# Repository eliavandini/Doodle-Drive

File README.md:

# Doodle-Drive
[Dokumentation](https://drive.google.com/file/d/1KEJBJEgJQQi80HQPX5YeS3n4wLadLSkT/view?usp=drive_link)

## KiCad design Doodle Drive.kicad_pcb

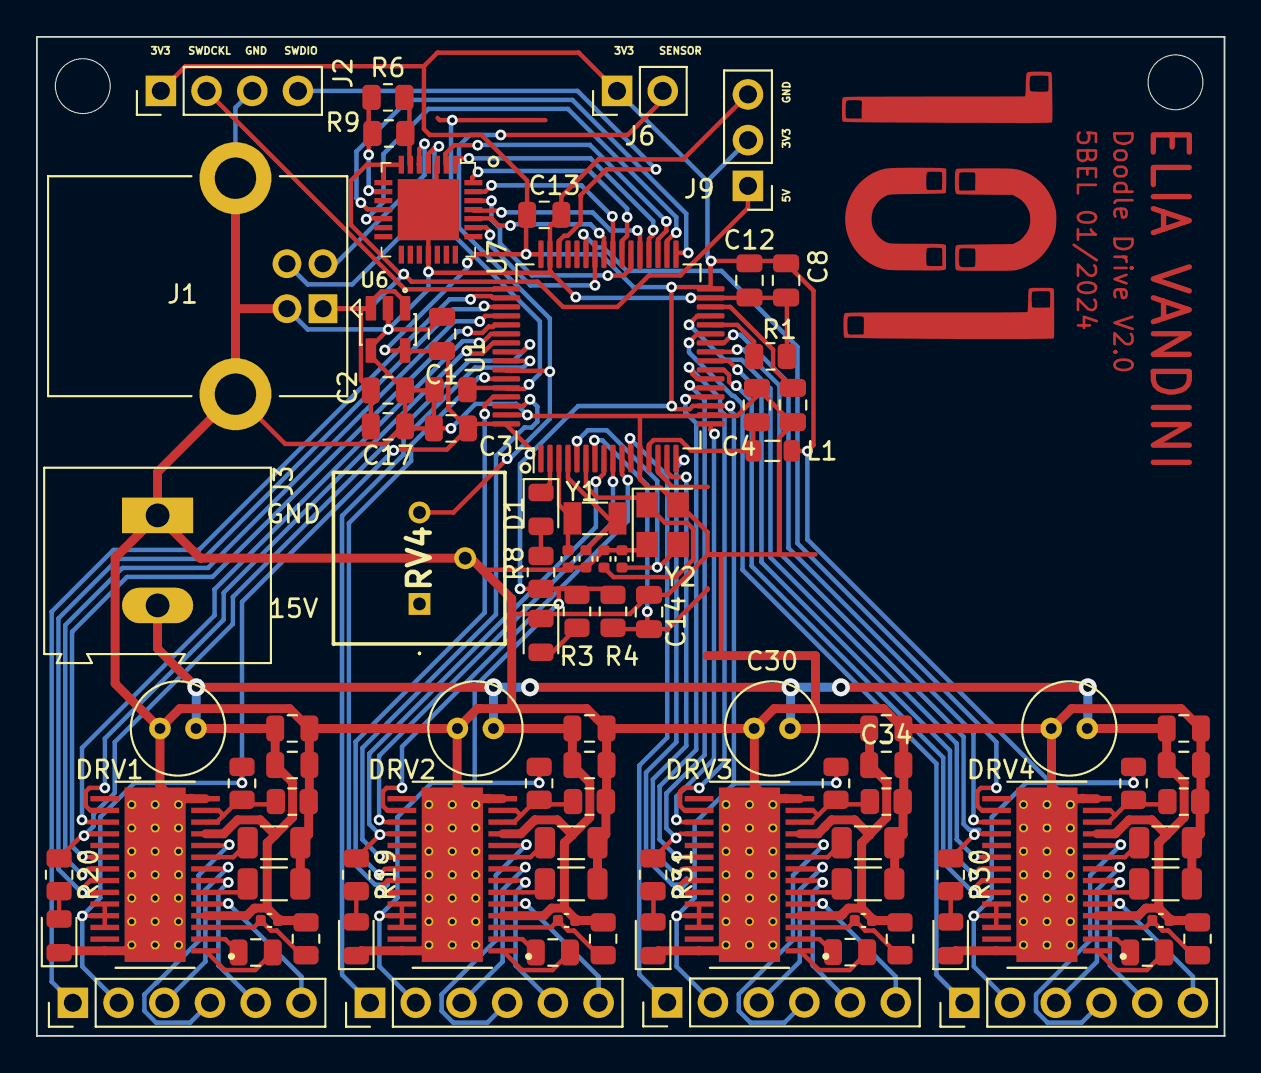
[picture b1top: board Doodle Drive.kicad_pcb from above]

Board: 2 copper layers, 66.0 x 55.5 mm, 91 parts (0 on the bottom side), 105 nets.

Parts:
C1, C17: 1uF; C_0805_2012Metric
C2, C3, C4, C8, C12, C13, C14, C20, C21, C23, C24, C31, C32, C33, C34: 100nF; C_0805_2012Metric
C5, C15, C25, C26: 10nF; C_0805_2012Metric
C6, C9: 18pF; C_0402_1005Metric
C7, C10: 15pF; C_0402_1005Metric
C11, C16, C27, C28: 100nF; C_0402_1005Metric
C18, C22, C29, C30: 10uF; C_Radial_D5.0mm_H5.0mm_P2.00mm
C19: 2.2uF; C_0805_2012Metric
D1: LED_GREEN; LED_0805_2012Metric
D2, D3, D4, D5, D6: LED_RED; LED_0805_2012Metric
DRV1, DRV2, DRV3, DRV4: DRV8825PWP; IC_TPS61196PWPRQ1
J1: USB_B; USB_B_Lumberg_2411_02_Horizontal
J2: PINHD_1x4_Male; PinHeader_1x04_P2.54mm_Vertical
J3: Screw_Terminal_01x02; TerminalBlock_Altech_AK300-2_P5.00mm
J4, J5, J7, J8: PINHD_1x6_Male; PinHeader_1x06_P2.54mm_Vertical
J6: PINHD_1x2_Male; PinHeader_1x02_P2.54mm_Vertical
J9: PINHD_1x3_Male; PinHeader_1x03_P2.54mm_Vertical
L1: 10uH; L_0805_2012Metric
R1, R2: 10k; R_0805_2012Metric
R3, R8, R19, R20, R30, R31: 5.1k; R_0805_2012Metric
R4: 0ohm; R_0805_2012Metric
R5, R7, R10, R22: 15k; R_0805_2012Metric
R6: 8.2k; R_0805_2012Metric
R9: 11k; R_0805_2012Metric
R11, R12, R21, R23: 9.1k; R_0805_2012Metric
R13, R14, R15, R16, R24, R25, R26, R27: 100m; R_1206_3216Metric
R17, R18, R28, R29: 1M; R_0805_2012Metric
RV4: R_Potentiometer; 3386P1473LF
U1: STM32F411RETx; LQFP-64_10x10mm_P0.5mm
U6: AP7343-33W5-7; SOT95P285X145-5N
U7: CP2102-GMR; VFQFN-28-1EP_5x5mm
Y1: 32.768KHz ±20ppm 12.5pF; Crystal_SMD_3215-2Pin_3.2x1.5mm
Y2: 25MHZ 12PF; Crystal_SMD_3225-4Pin_3.2x2.5mm

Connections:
+3V3: C1.2, C3.2, C8.2, C12.2, C13.2, DRV1.24 (MODE0), DRV1.25 (MODE1), DRV1.26 (MODE2), DRV2.24 (MODE0), DRV2.25 (MODE1), DRV2.26 (MODE2), DRV3.24 (MODE0), DRV3.25 (MODE1), DRV3.26 (MODE2), DRV4.24 (MODE0), DRV4.25 (MODE1), DRV4.26 (MODE2), J2.1, J4.2, J5.2, J6.1, J7.2, J8.2, J9.2, L1.1, R3.2, R4.2, R5.2, R7.2, R8.2, R10.2, R22.2, U1.19 (VDD), U1.32 (VDD), U1.48 (VDD), U1.64 (VDD), U6.5 (VOUT)
+5V: C2.2, C17.1, J1.1 (VBUS), J9.1, U6.1 (VIN), U6.3 (EN), U7.7 (REGIN), U7.8 (VBUS)
+15V: C11.1, C16.1, C18.2, C20.1, C21.1, C22.2, C23.1, C24.1, C27.1, C28.1, C29.2, C30.2, C31.1, C32.1, C33.1, C34.1, DRV1.4 (VMA), DRV1.11 (VMB), DRV2.4 (VMA), DRV2.11 (VMB), DRV3.4 (VMA), DRV3.11 (VMB), DRV4.4 (VMA), DRV4.11 (VMB), J3.2, R17.2, R18.2, R28.2, R29.2
BOOT0: R2.1, U1.60 (BOOT0)
DIR1: DRV1.20 (DIR), U1.53 (PC12)
DIR2: DRV2.20 (DIR), U1.62 (PB9)
DIR3: DRV3.20 (DIR), U1.20 (PA4)
DIR4: DRV4.20 (DIR), U1.29 (PB10)
GND: C1.1, C2.1, C3.1, C4.1, C6.1, C7.1, C8.1, C9.1, C10.2, C12.1, C13.1, C14.1, C17.2, C18.1, C19.2, C20.2, C21.2, C22.1, C23.2, C24.2, C29.1, C30.1, C31.2, C32.2, C33.2, C34.2, D2.1 (K), D3.1 (K), D4.1 (K), D5.1 (K), D6.1 (K), DRV1.14 (GND), DRV1.28 (GND), DRV1.29 (EXP), DRV1.30 (EXP), DRV1.31 (EXP), DRV1.32 (EXP), DRV1.33 (EXP), DRV1.34 (EXP), DRV1.35 (EXP), DRV1.36 (EXP), DRV1.37 (EXP), DRV1.38 (EXP), DRV1.39 (EXP), DRV1.40 (EXP), DRV1.41 (EXP), DRV1.42 (EXP), DRV1.43 (EXP), DRV1.44 (EXP), DRV1.45 (EXP), DRV1.46 (EXP), DRV1.47 (EXP), DRV1.48 (EXP), DRV1.49 (EXP), DRV1.50 (EXP), DRV2.14 (GND), DRV2.28 (GND), DRV2.29 (EXP), DRV2.30 (EXP), DRV2.31 (EXP), DRV2.32 (EXP), DRV2.33 (EXP), DRV2.34 (EXP), DRV2.35 (EXP), DRV2.36 (EXP), DRV2.37 (EXP), DRV2.38 (EXP), DRV2.39 (EXP), DRV2.40 (EXP), DRV2.41 (EXP), DRV2.42 (EXP), DRV2.43 (EXP), DRV2.44 (EXP), DRV2.45 (EXP), DRV2.46 (EXP), DRV2.47 (EXP), DRV2.48 (EXP), DRV2.49 (EXP), DRV2.50 (EXP), DRV3.14 (GND), DRV3.28 (GND), DRV3.29 (EXP), DRV3.30 (EXP), DRV3.31 (EXP), DRV3.32 (EXP), DRV3.33 (EXP), DRV3.34 (EXP), DRV3.35 (EXP), DRV3.36 (EXP), DRV3.37 (EXP), DRV3.38 (EXP), DRV3.39 (EXP), DRV3.40 (EXP), DRV3.41 (EXP), DRV3.42 (EXP), DRV3.43 (EXP), DRV3.44 (EXP), DRV3.45 (EXP), DRV3.46 (EXP), DRV3.47 (EXP), DRV3.48 (EXP), DRV3.49 (EXP), DRV3.50 (EXP), DRV4.14 (GND), DRV4.28 (GND), DRV4.29 (EXP), DRV4.30 (EXP), DRV4.31 (EXP), DRV4.32 (EXP), DRV4.33 (EXP), DRV4.34 (EXP), DRV4.35 (EXP), DRV4.36 (EXP), DRV4.37 (EXP), DRV4.38 (EXP), DRV4.39 (EXP), DRV4.40 (EXP), DRV4.41 (EXP), DRV4.42 (EXP), DRV4.43 (EXP), DRV4.44 (EXP), DRV4.45 (EXP), DRV4.46 (EXP), DRV4.47 (EXP), DRV4.48 (EXP), DRV4.49 (EXP), DRV4.50 (EXP), J1.4 (GND), J1.5 (Shield), J2.3, J3.1, J9.3, R1.1, R2.2, R11.1, R12.1, R13.2, R14.2, R15.2, R16.2, R21.1, R23.1, R24.2, R25.2, R26.2, R27.2, RV4.2, U1.12 (VSSA), U1.18 (VSS), U1.31 (VSS), U1.47 (VSS), U1.63 (VSS), U6.2 (GND), U6.4 (NC), U7.3 (GND), U7.18 (VPP), U7.29 (GND_PAD), Y2.2, Y2.4
unnamed: D1.2 (A), R8.1
unnamed: D2.2 (A), R3.1
unnamed: D3.2 (A), R19.2
unnamed: D4.2 (A), R20.2
unnamed: D5.2 (A), R30.2
unnamed: D6.2 (A), R31.2
unnamed: DRV1.5 (AOUT1), J5.6
unnamed: DRV1.7 (AOUT2), J5.5
unnamed: DRV1.12 (AVREF), DRV1.13 (BVREF), R7.1, R21.2
unnamed: DRV1.10 (BOUT1), J5.4
unnamed: DRV1.8 (BOUT2), J5.3
unnamed: C15.2, DRV1.1 (CP1)
unnamed: C15.1, DRV1.2 (CP2)
unnamed: DRV1.6 (ISENA), R15.1
unnamed: DRV1.9 (ISENB), R16.1
unnamed: C16.2, DRV1.3 (VCP), R17.1
unnamed: DRV2.5 (AOUT1), J7.6
unnamed: DRV2.7 (AOUT2), J7.5
unnamed: DRV2.12 (AVREF), DRV2.13 (BVREF), R5.1, R12.2
unnamed: DRV2.10 (BOUT1), J7.4
unnamed: DRV2.8 (BOUT2), J7.3
unnamed: C5.2, DRV2.1 (CP1)
unnamed: C5.1, DRV2.2 (CP2)
unnamed: DRV2.6 (ISENA), R13.1
unnamed: DRV2.9 (ISENB), R14.1
unnamed: C11.2, DRV2.3 (VCP), R18.1
unnamed: DRV3.5 (AOUT1), J8.6
unnamed: DRV3.7 (AOUT2), J8.5
unnamed: DRV3.12 (AVREF), DRV3.13 (BVREF), R22.1, R23.2
unnamed: DRV3.10 (BOUT1), J8.4
unnamed: DRV3.8 (BOUT2), J8.3
unnamed: C26.2, DRV3.1 (CP1)
unnamed: C26.1, DRV3.2 (CP2)
unnamed: DRV3.6 (ISENA), R26.1
unnamed: DRV3.9 (ISENB), R27.1
unnamed: C28.2, DRV3.3 (VCP), R29.1
unnamed: DRV4.5 (AOUT1), J4.6
unnamed: DRV4.7 (AOUT2), J4.5
unnamed: DRV4.12 (AVREF), DRV4.13 (BVREF), R10.1, R11.2
unnamed: DRV4.10 (BOUT1), J4.4
unnamed: DRV4.8 (BOUT2), J4.3
unnamed: C25.2, DRV4.1 (CP1)
unnamed: C25.1, DRV4.2 (CP2)
unnamed: DRV4.6 (ISENA), R24.1
unnamed: DRV4.9 (ISENB), R25.1
unnamed: C27.2, DRV4.3 (VCP), R28.1
unnamed: J1.3 (D+), U7.4 (D+)
unnamed: J1.2 (D-), U7.5 (D-)
unnamed: C19.1, U1.30 (VCAP1)
unnamed: R6.1, R9.1, U7.9 (RST)
unnamed: R6.2, R9.2, U7.6 (VDD)
PA1: DRV3.21 (NENBL), U1.15 (PA1)
PA2: DRV3.22 (STEP), U1.16 (PA2)
PA3: DRV3.17 (NSLEEP), U1.17 (PA3)
PA5: DRV3.18 (NFAULT), R31.1, U1.21 (PA5)
PA6: DRV3.16 (~NRESET), U1.22 (PA6)
PA7: DRV4.22 (STEP), U1.23 (PA7)
PA8: U1.41 (PA8), U7.24 (~RTS)
PA9: U1.42 (PA9), U7.23 (~CTS)
PA10: DRV4.16 (~NRESET), U1.43 (PA10)
PA13: J2.4, U1.46 (PA13)
PA14: J2.2, U1.49 (PA14)
PA15: J5.1, U1.50 (PA15)
PB0: DRV4.17 (NSLEEP), U1.26 (PB0)
PB1: J4.1, U1.27 (PB1)
PB2: R1.2, U1.28 (PB2)
PB3: DRV1.16 (~NRESET), U1.55 (PB3)
PB4: DRV1.18 (NFAULT), R20.1, U1.56 (PB4)
PB5: J7.1, U1.57 (PB5)
PB6: J6.2, RV4.3, U1.58 (PB6)
PB7: DRV2.22 (STEP), U1.59 (PB7)
PB8: DRV2.21 (NENBL), U1.61 (PB8)
PB12: U1.33 (PB12), U7.11 (~SUSPEND)
PB13: U1.34 (PB13), U7.12 (SUSPEND)
PB14: U1.35 (PB14), U7.2 (~RI)
PB15: U1.36 (PB15), U7.1 (~DCD)
PC0: DRV2.18 (NFAULT), R19.1, U1.8 (PC0)
PC1: DRV2.17 (NSLEEP), U1.9 (PC1)
PC2: DRV2.16 (~NRESET), U1.10 (PC2)
PC3: J8.1, U1.11 (PC3)
PC4: DRV4.21 (NENBL), U1.24 (PC4)
PC5: DRV4.18 (NFAULT), R30.1, U1.25 (PC5)
PC6: U1.37 (PC6), U7.25 (RXD)
PC7: U1.38 (PC7), U7.26 (TXD)
PC8: U1.39 (PC8), U7.28 (~DTR)
PC9: U1.40 (PC9), U7.27 (~DSR)
PC10: DRV1.22 (STEP), U1.51 (PC10)
PC11: DRV1.21 (NENBL), U1.52 (PC11)
PC13: D1.1 (K), U1.2 (PC13)
PC14: C7.2, U1.3 (PC14), Y1.2
PC15: C10.1, U1.4 (PC15), Y1.1
PD2: DRV1.17 (NSLEEP), U1.54 (PD2)
PH0: C6.2, U1.5 (PH0), Y2.3
PH1: C9.2, U1.6 (PH1), Y2.1
VREF+: C4.2, L1.2, U1.13 (VDDA)
~RST: C14.2, R4.1, U1.7 (NRST)

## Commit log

2023-11-08 cleaned up main schematic
2023-11-08 Divide DRV8825s in two sheets, and connect their pins to stm32
2023-11-08 fixed few errors, added test points
2023-11-09 add CP2102 USB to UART chip
2023-11-10 deleted unnecessary testpoints
2023-11-10 started work on pcb
2023-11-11 fixed voltage dividers, roughly arrangenged components on pcb, set up 3V3 and GND area
2023-11-12 routed some paths on schematic. need to rearrange driver pins and come up with solution with motor poer supply
2023-11-13 temporarly detached testpoints
2023-11-14 routet Motor Driver modules, reattached and placed testpoints
2023-11-17 moved stuff closer, changed testpoint footprint, connected VM
2023-11-22 finished PCB. DRC 0 errors
2023-11-24 last polishing on pcb v1. ich isch abgabe dc
2023-11-30 completly reroutet EVERYTHING
2023-12-05 deTommaso approved version
2023-12-06 bestellte version
2024-01-04 reworked single motor drive module
2024-01-05 restiched everything and removed polygons
2024-01-10 placed jlcpcb basic buttons and rerouted unchristliche wires
2024-01-10 added 3d models from the world wide web
2024-01-18 moved every third party content to lib, added 3d models and also just finished rerouting EVERYTHING. also added pcb addon for st-link so i dont accidentally verole anymore
2024-01-19 fixed variuopus stuff, this is probaly the bestellte version
2024-01-28 added pins for motor edge sensors, reroutet driver modules, removed module potentiometer, made everything more compact, fixed labels
2024-01-29 fixed Serial connection, and various improvments
2024-06-10 letzter code
